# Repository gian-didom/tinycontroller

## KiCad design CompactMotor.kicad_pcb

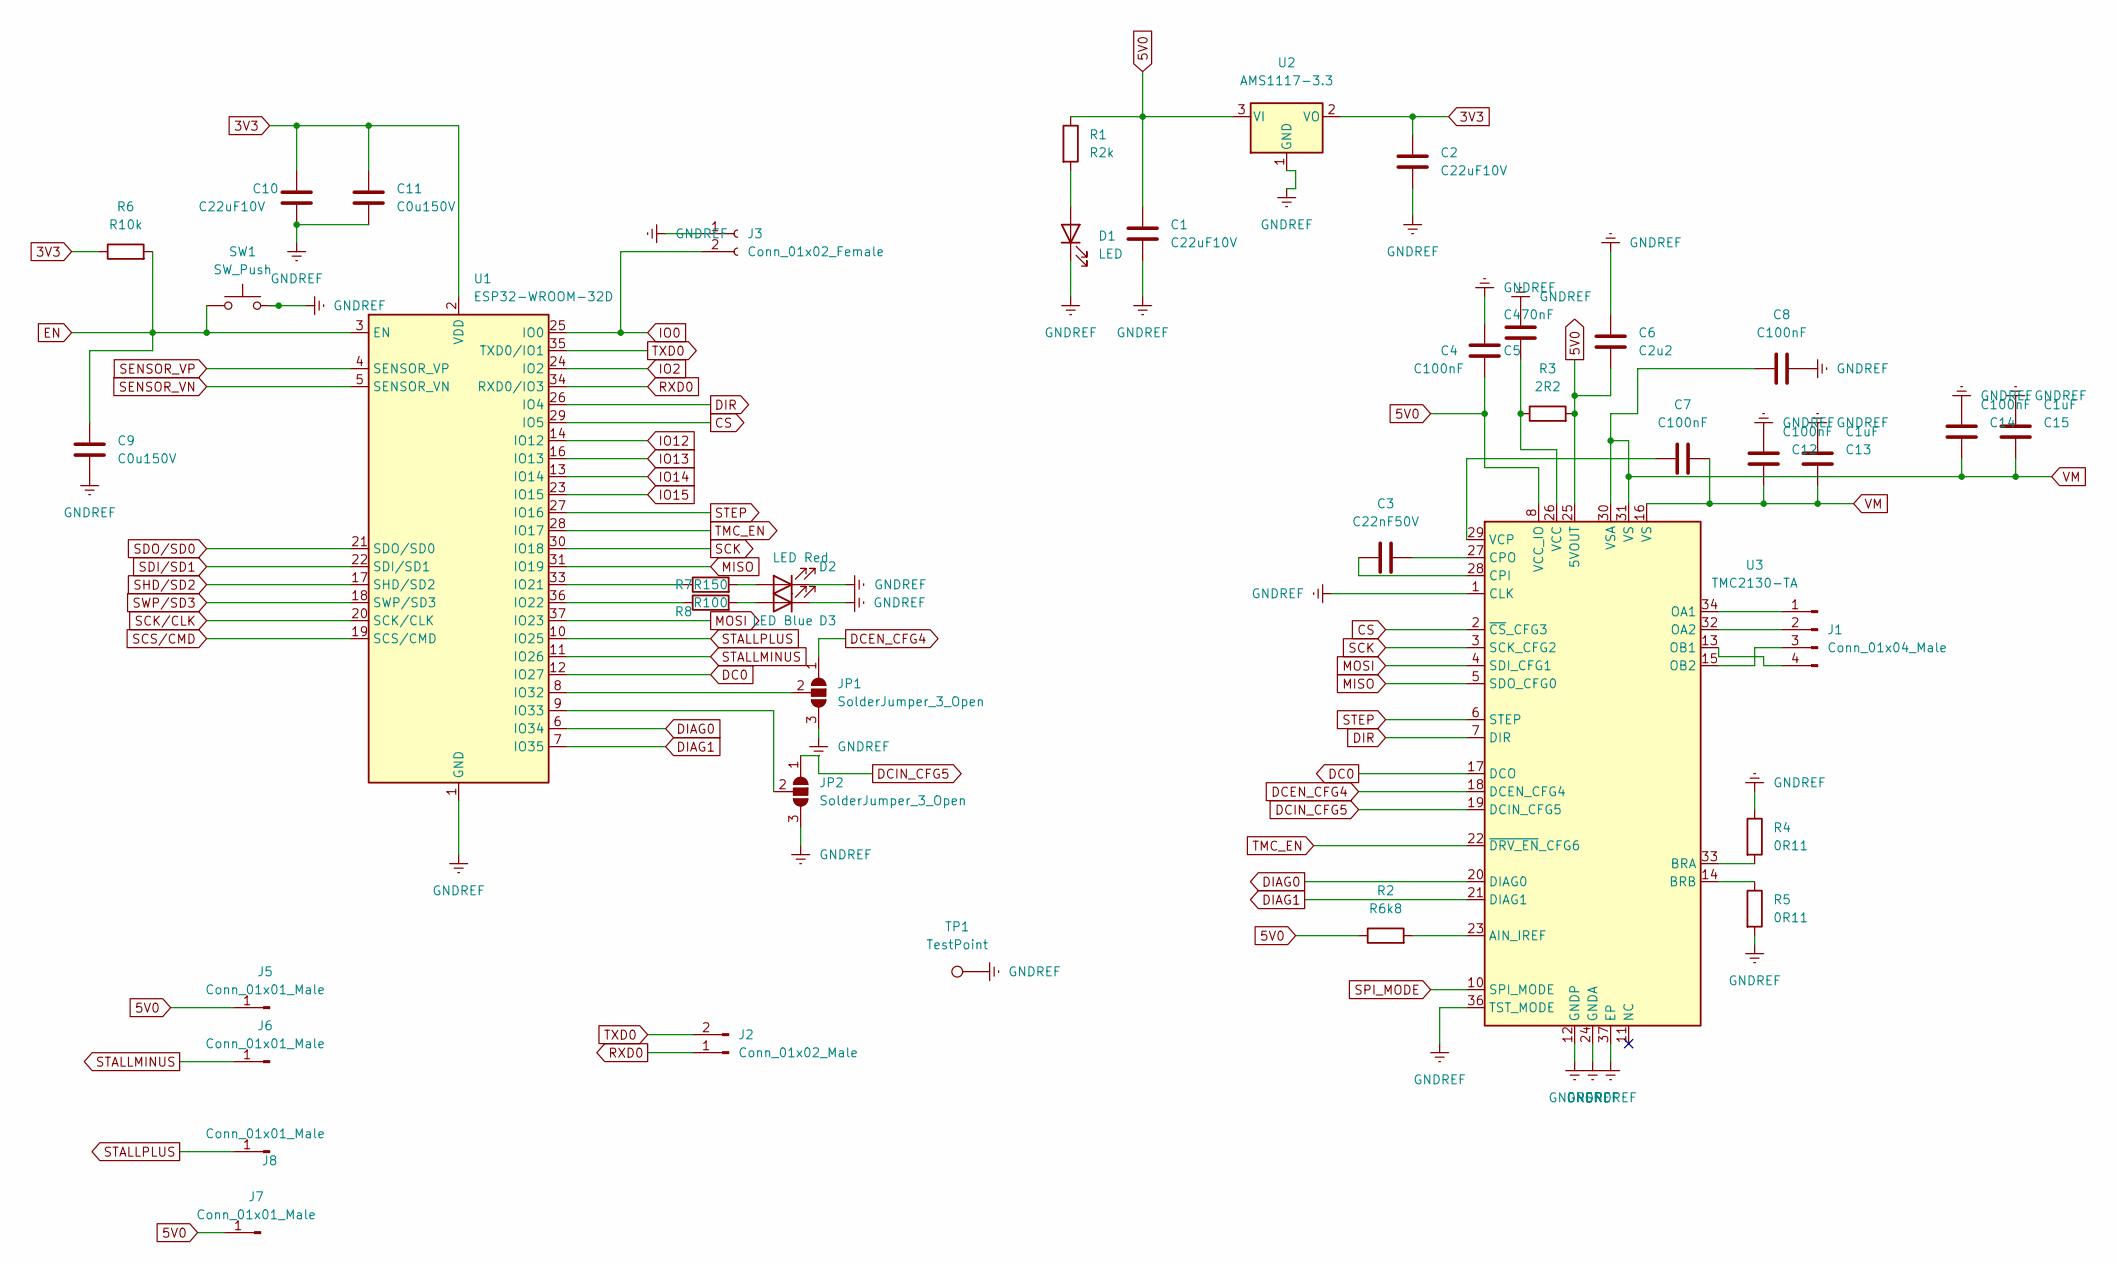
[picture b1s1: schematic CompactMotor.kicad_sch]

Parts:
C1, C2, C10: C22uF10V; C_0603_1608Metric
C3: C22nF50V; C_0603_1608Metric
C4, C7, C8, C12, C14: C100nF; C_0603_1608Metric
C5: C470nF; C_0603_1608Metric
C6: C2u2; C_0603_1608Metric
C9, C11: C0u150V; C_0603_1608Metric
C13, C15: C1uF; C_0603_1608Metric
D1: LED; LED_0402_1005Metric
D2: LED Red; LED_0402_1005Metric
D3: LED Blue; LED_0402_1005Metric
J1: Conn_01x04_Male; PinHeader_1x04_P2.54mm_Horizontal
J2: Conn_01x02_Male; PinHeader_1x02_P2.54mm_Horizontal
J3: Conn_01x02_Female; PinHeader_1x02_P2.54mm_Horizontal
J5, J6, J7, J8: Conn_01x01_Male; PinHeader_1x01_P2.54mm_Horizontal
JP1, JP2: SolderJumper_3_Open; SolderJumper-3_P1.3mm_Open_RoundedPad1.0x1.5mm
R1: R2k; R_0402_1005Metric
R2: R6k8; R_0402_1005Metric
R3: 2R2; R_0402_1005Metric
R4, R5: 0R11; R_0402_1005Metric
R6: R10k; R_0402_1005Metric
R7: R150; R_0402_1005Metric
R8: R100; R_0402_1005Metric
SW1: SW_Push; SW1AB-260-10T28
TP1: TestPoint; TestPoint_Pad_4.0x4.0mm
U1: ESP32-WROOM-32D; ESP32-WROOM-32
U2: AMS1117-3.3; SOT-223-3_TabPin2
U3: TMC2130-TA; QFN-36-1EP_5x6mm_P0.5mm_EP3.6x4.1mm

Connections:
3V3: C2.1, C10.1, C11.1, R6.1, U1.2 (VDD), U2.2 (VO)
5V0: C1.1, C4.2, C6.2, J5.1, J7.1, R1.1, R2.1, R3.2, U2.3 (VI), U3.8 (VCC_IO), U3.25 (5VOUT)
CS: U1.29 (IO5), U3.2 (~CS_CFG3)
DC0: U1.12 (IO27), U3.17 (DCO)
DCEN_CFG4: JP1.1 (A), U3.18 (DCEN_CFG4)
DCIN_CFG5: JP2.1 (A), U3.19 (DCIN_CFG5)
DIAG0: U1.6 (IO34), U3.20 (DIAG0)
DIAG1: U1.7 (IO35), U3.21 (DIAG1)
DIR: U1.26 (IO4), U3.7 (DIR)
EN: C9.1, R6.2, SW1.1, U1.3 (EN)
GNDREF: C1.2, C2.2, C4.1, C5.1, C6.1, C8.1, C9.2, C10.2, C11.2, C12.2, C13.1, C14.2, C15.1, D1.1 (K), D2.1 (K), D3.1 (K), J3.1, JP1.3 (B), JP2.3 (B), R4.1, R5.2, SW1.2, TP1.1, U1.1 (GND), U1.15 (GND), U1.38 (GND), U1.39 (GND), U2.1 (GND), U3.1 (CLK), U3.12 (GNDP), U3.24 (GNDA), U3.35 (GNDP), U3.36 (TST_MODE), U3.37 (EP)
IO0: J3.2, U1.25 (IO0)
IO2: U1.24 (IO2)
IO12: U1.14 (IO12)
IO13: U1.16 (IO13)
IO14: U1.13 (IO14)
IO15: U1.23 (IO15)
MISO: U1.31 (IO19), U3.5 (SDO_CFG0)
MOSI: U1.37 (IO23), U3.4 (SDI_CFG1)
unnamed: C3.1, U3.28 (CPI)
unnamed: C3.2, U3.27 (CPO)
unnamed: C5.2, R3.1, U3.26 (VCC)
unnamed: C7.2, U3.29 (VCP)
unnamed: D1.2 (A), R1.2
unnamed: D2.2 (A), R7.2
unnamed: D3.2 (A), R8.2
unnamed: J1.1, U3.34 (OA1)
unnamed: J1.2, U3.32 (OA2)
unnamed: J1.3, U3.15 (OB2)
unnamed: J1.4, U3.13 (OB1)
unnamed: JP1.2 (C), U1.8 (IO32)
unnamed: JP2.2 (C), U1.9 (IO33)
unnamed: R2.2, U3.23 (AIN_IREF)
unnamed: R4.2, U3.33 (BRA)
unnamed: R5.1, U3.14 (BRB)
unnamed: R7.1, U1.33 (IO21)
unnamed: R8.1, U1.36 (IO22)
RXD0: J2.1, U1.34 (RXD0/IO3)
SCK: U1.30 (IO18), U3.3 (SCK_CFG2)
SCK/CLK: U1.20 (SCK/CLK)
SCS/CMD: U1.19 (SCS/CMD)
SDI/SD1: U1.22 (SDI/SD1)
SDO/SD0: U1.21 (SDO/SD0)
SENSOR_VN: U1.5 (SENSOR_VN)
SENSOR_VP: U1.4 (SENSOR_VP)
SHD/SD2: U1.17 (SHD/SD2)
SPI_MODE: U3.10 (SPI_MODE)
STALLMINUS: J6.1, U1.11 (IO26)
STALLPLUS: J8.1, U1.10 (IO25)
STEP: U1.27 (IO16), U3.6 (STEP)
SWP/SD3: U1.18 (SWP/SD3)
TMC_EN: U1.28 (IO17), U3.22 (~DRV_EN_CFG6)
TXD0: J2.2, U1.35 (TXD0/IO1)
VM: C7.1, C8.2, C12.1, C13.2, C14.1, C15.2, U3.16 (VS), U3.30 (VSA), U3.31 (VS)

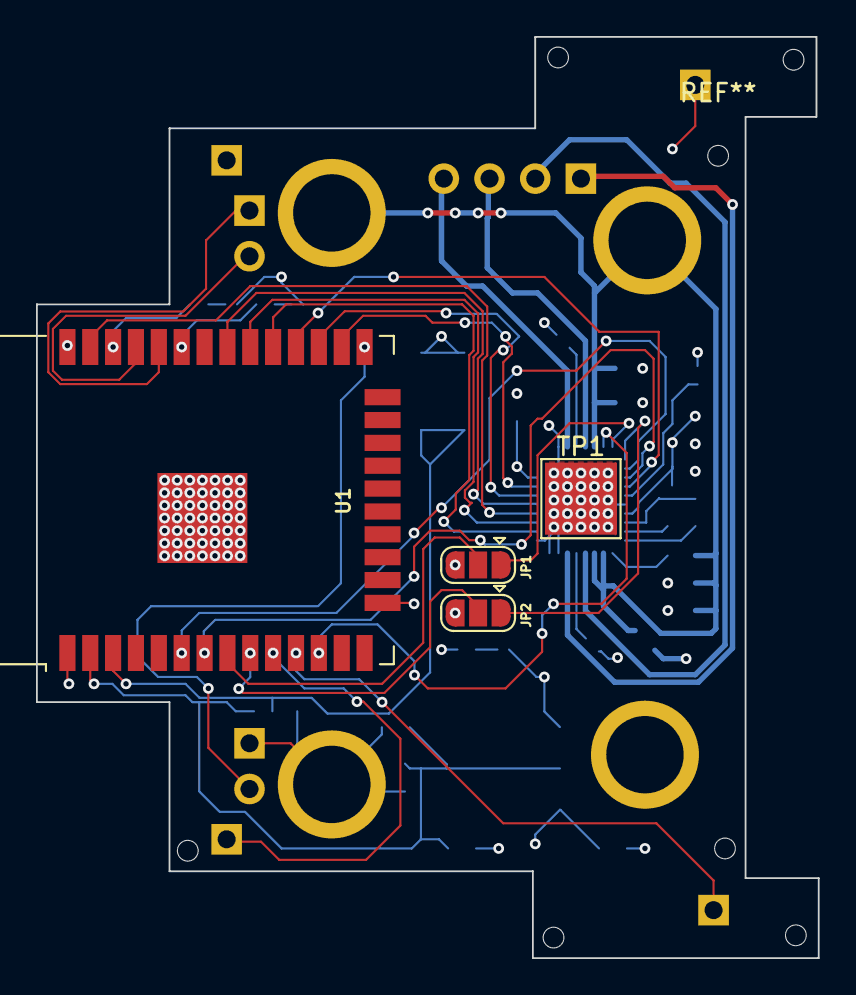
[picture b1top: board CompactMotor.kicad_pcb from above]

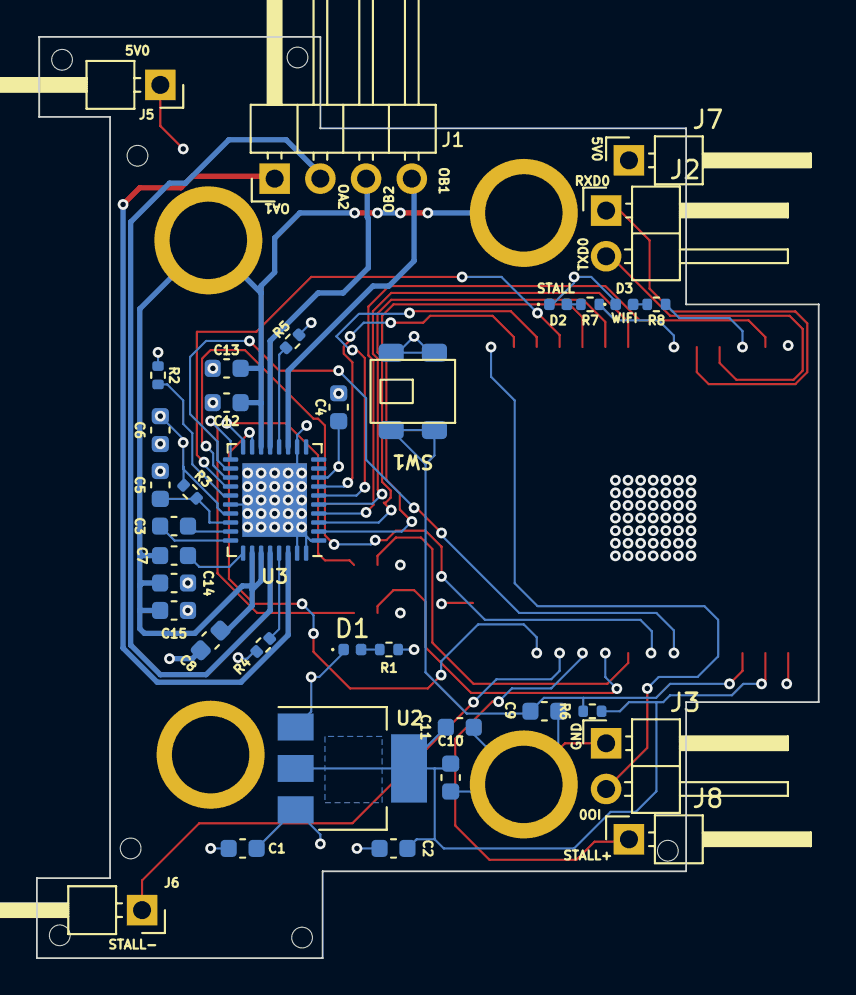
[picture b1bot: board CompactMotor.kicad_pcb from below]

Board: 4 copper layers, 43.4 x 51.2 mm, 45 parts (36 on the bottom side), 40 nets.

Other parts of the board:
 : MountingHole_4.3mm_M4
  : MotorBracker
 #2,  #3,  #4: MountingHole_4.3mm_M4

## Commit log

2022-03-09 Rerouting for holes
2022-03-10 Only trx-rx
2022-03-11 Only trx missing
2022-03-11 CLP BOM
